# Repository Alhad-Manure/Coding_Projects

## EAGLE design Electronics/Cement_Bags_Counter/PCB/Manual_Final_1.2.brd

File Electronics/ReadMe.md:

All Embedded Electronics related codes.

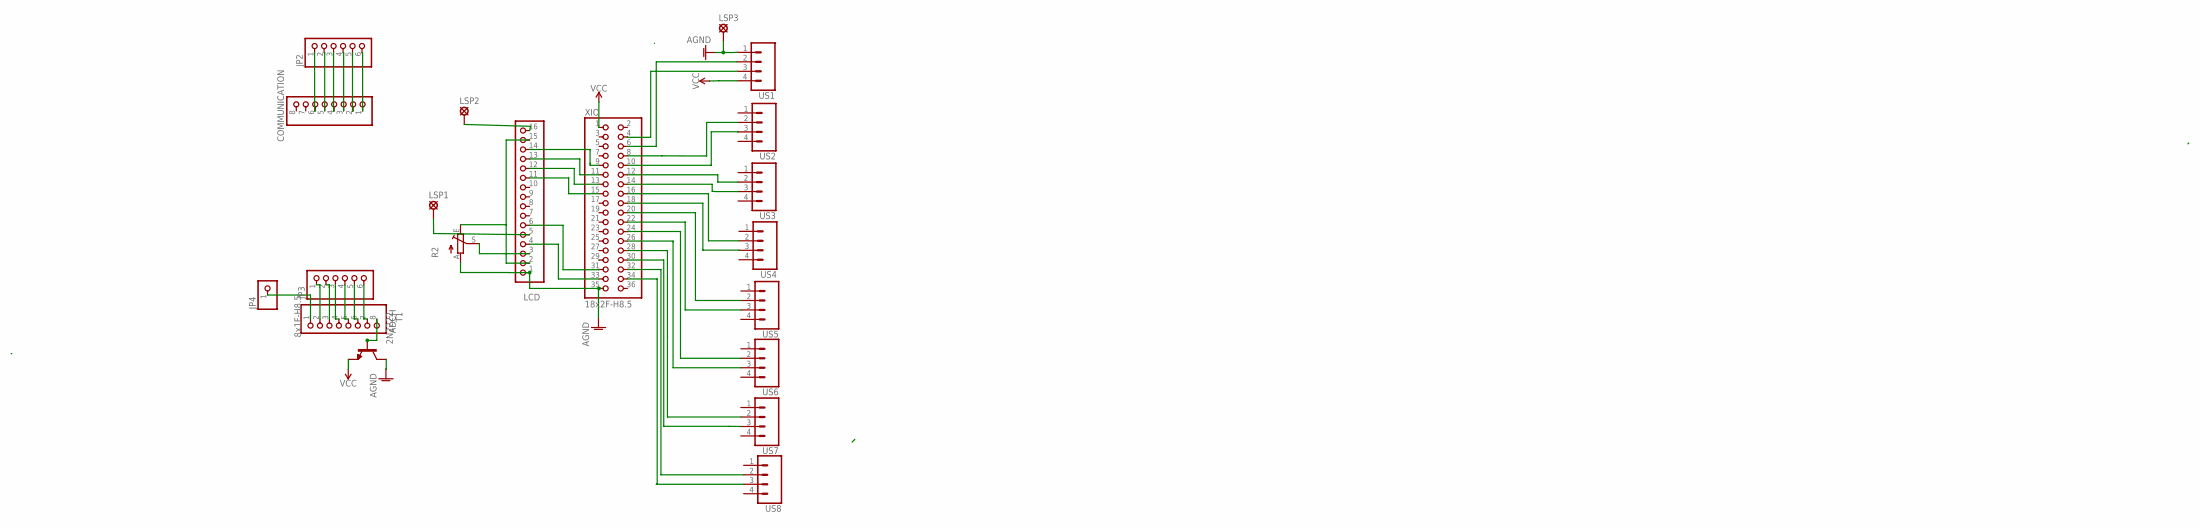
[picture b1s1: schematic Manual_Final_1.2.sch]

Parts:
ADCH: 8x1F-H8.5; 1X08
COMMUNICATION: 8x1F-H8.5; 1X08
JP2, JP3: PINHD-1X6; 1X06
JP4: PINHD-1X1; 1X01
LCD: PINHD-1X16; 1X16
LSP1, LSP2, LSP3: SE14
R2: TRIM_EU-RS3; RS3
T1: 2N2222; TO92-EBC-OVAL
US1, US2, US3, US4, US5, US6, US7, US8: CONN_04LOCK_LONGPADS; 1X04_LOCK_LONGPADS
XIO: 18x2F-H8.5; 2X18

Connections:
AGND: LCD.1, LSP3.MP, R2.A, T1.C, US1.1, XIO.35
unnamed: ADCH.8, T1.B
unnamed: COMMUNICATION.1, JP2.6
unnamed: US1.3, XIO.4
unnamed: US1.2, XIO.6
unnamed: US2.2, XIO.8
unnamed: US2.3, XIO.10
unnamed: US3.2, XIO.12
unnamed: US5.2, XIO.20
unnamed: US4.2, XIO.16
unnamed: US4.3, XIO.18
unnamed: US5.3, XIO.22
unnamed: US6.2, XIO.24
unnamed: US6.3, XIO.26
unnamed: US7.2, XIO.28
unnamed: US7.3, XIO.30
unnamed: US8.2, XIO.32
unnamed: US3.3, XIO.14
unnamed: US8.3, XIO.34
unnamed: LCD.2, LCD.15, R2.E
unnamed: LCD.3, R2.S
unnamed: LCD.4, XIO.33
unnamed: LCD.6, XIO.31
unnamed: LCD.14, XIO.9
unnamed: LCD.13, XIO.11
unnamed: LCD.12, XIO.13
unnamed: COMMUNICATION.2, JP2.5
unnamed: COMMUNICATION.3, JP2.4
unnamed: COMMUNICATION.4, JP2.3
unnamed: COMMUNICATION.5, JP2.2
unnamed: COMMUNICATION.6, JP2.1
unnamed: ADCH.7, JP3.6
unnamed: ADCH.6, JP3.5
unnamed: LCD.16, LSP2.MP
unnamed: LCD.5, LSP1.MP
unnamed: LCD.11, XIO.15
unnamed: ADCH.5, JP3.4
unnamed: ADCH.4, JP3.3
unnamed: ADCH.3, JP3.2
unnamed: ADCH.2, JP3.1
unnamed: ADCH.1, JP4.1
VCC: T1.E, US1.4, XIO.1

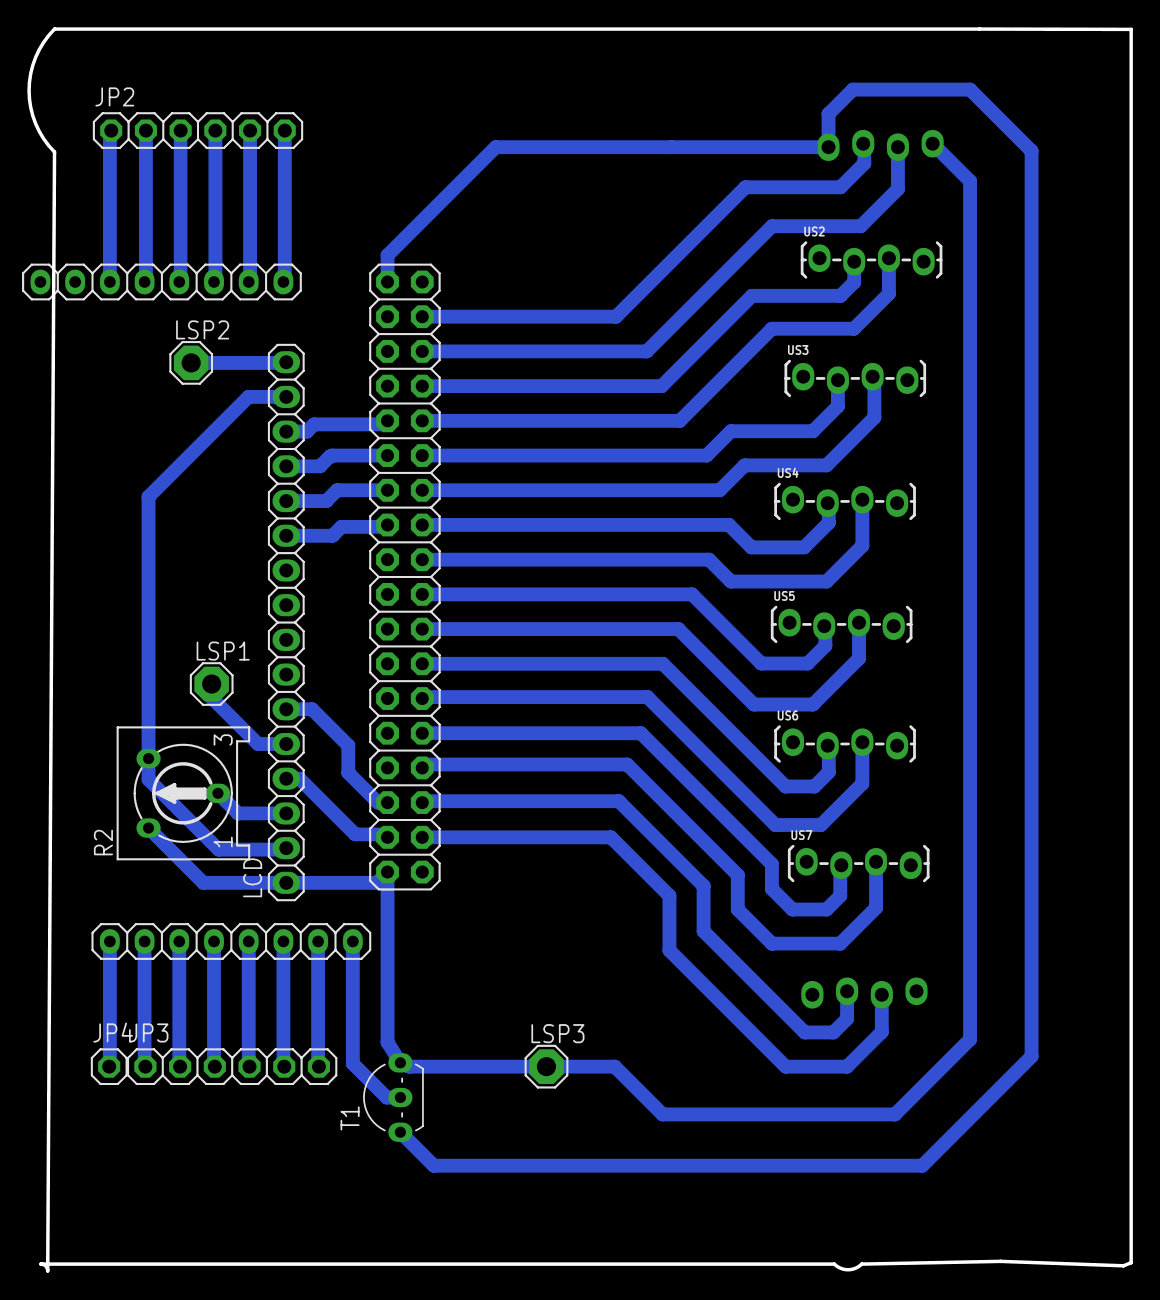
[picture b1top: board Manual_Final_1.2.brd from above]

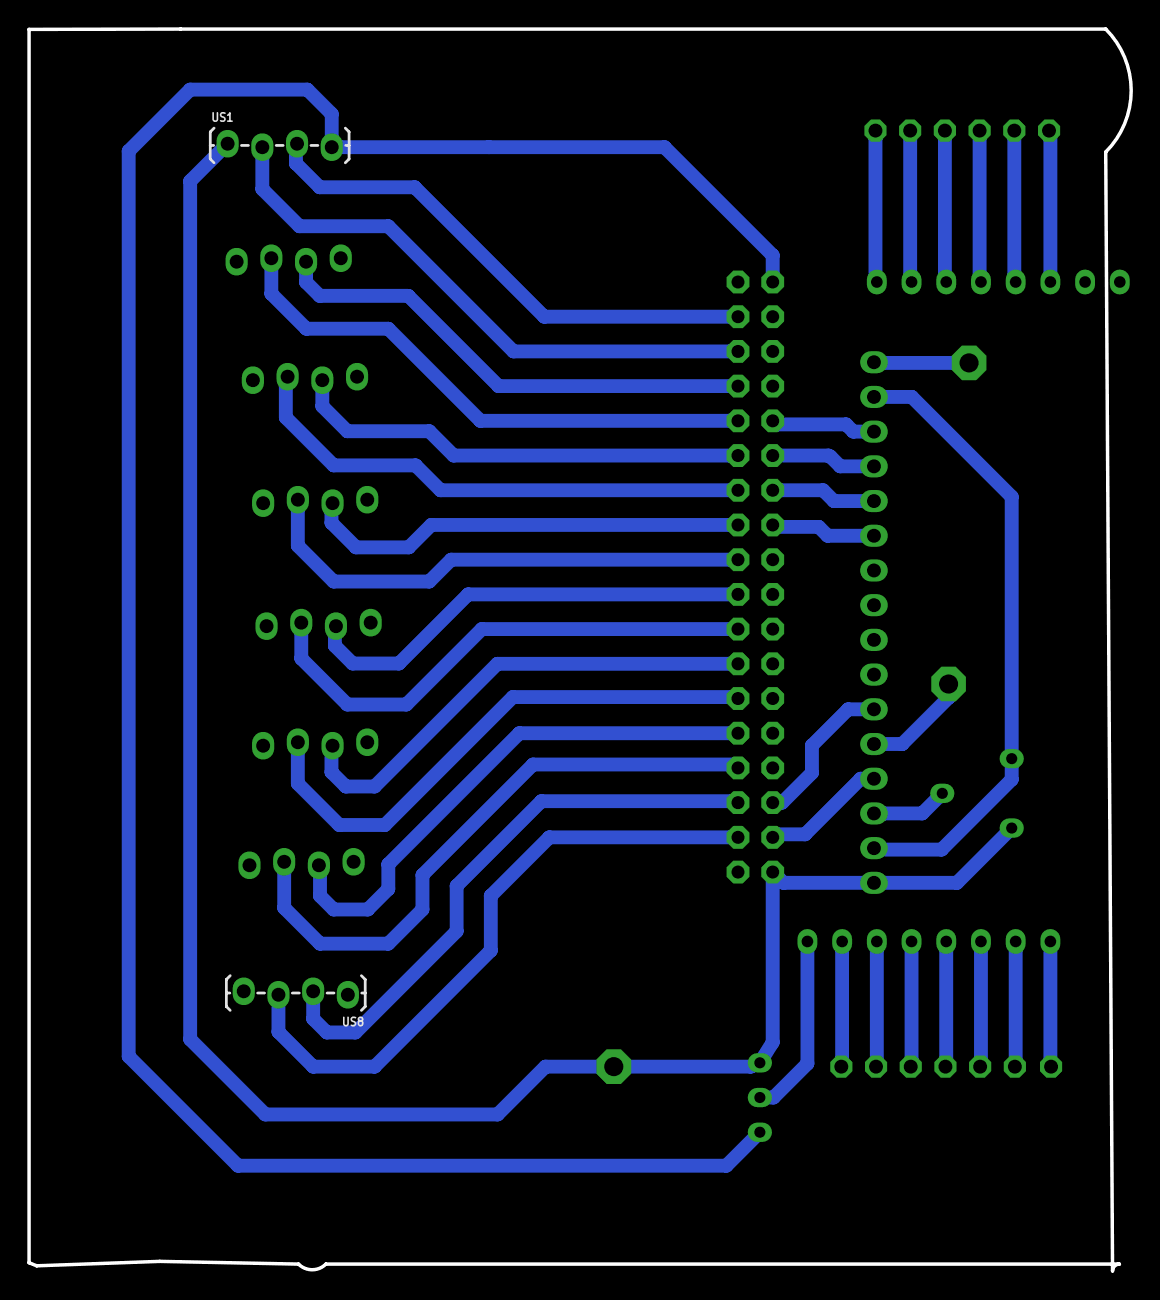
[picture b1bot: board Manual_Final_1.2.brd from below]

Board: 2 copper layers, 80.7 x 90.9 mm, 20 parts (2 on the bottom side), 42 nets.

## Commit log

2021-11-13 Rename Musical_Dancing_LEDs_&_Fountain/Musical_Multi_LEDs_Fountain2/Musical_Multi_LEDs_Fountain2.ino to Musical_Dancing_LEDs_&_Fountain/Musical_Multi_LEDs_Fountain/Musical_Multi_LEDs_Fountain.ino
2021-11-13 Create Musical_Dancing_LEDs
2021-11-13 Rename Holonomic_Drive/Manual_Drive_Without_encoder_4/Manual_Drive_Without_encoder_4.ino to Holonomic_Drive/Manual_Drive_Without_encoder/Manual_Drive_Without_encoder.ino
2022-04-13 Rename Holonomic_Drive/Manual_Drive_Without_encoder/Manual_Drive_Without_encoder.ino to Electronics/Holonomic_Drive/Manual_Drive_Without_encoder/Manual_Drive_Without_encoder.ino
2022-04-13 Rename Multi_Terrain_Robot/Robot_Car/Robot_Car.ino to Electronics/Multi_Terrain_Robot/Robot_Car/Robot_Car.ino
2022-04-13 Rename Multi_Terrain_Robot/Remote_Controle/Remote_Controle.ino to Electronics/Multi_Terrain_Robot/Remote_Controle/Remote_Controle.ino
2022-04-13 Rename Musical_Dancing_LEDs_&_Fountain/Musical_Multi_LEDs_Fountain/Musical_Multi_LEDs_Fountain.ino to Electronics/Musical_Dancing_LEDs_&_Fountain/Musical_Multi_LEDs_Fountain/Musical_Multi_LEDs_Founta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
2022-04-13 Rename Musical_Dancing_LEDs_&_Fountain/Musical_Spectrum_LEDs_Fountain/Musical_Spectrum_LEDs_Fountain.ino to Electronics/Musical_Dancing_LEDs_&_Fountain/Musical_Spectrum_LEDs_Fountain/Musical_Spectrum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
2022-04-13 Rename SecurityCam/CameraWeb/CameraWeb.ino to Electronics/SecurityCam/CameraWeb/Musical_Spectrum_LEDs_Fountain.ino
2022-04-13 Rename Musical_Spectrum_LEDs_Fountain.ino to CameraWeb5.ino
2022-04-13 Rename SecurityCam/CameraWeb/app_httpd.cpp to Electronics/SecurityCam/CameraWeb/app_httpd.cpp
2022-04-13 Rename SecurityCam/CameraWeb/camera_index.h to Electronics/SecurityCam/CameraWeb/camera_index.h
2022-04-13 Rename SecurityCam/CameraWeb/camera_pins.h to Electronics/SecurityCam/CameraWeb/camera_pins.h
2022-04-13 Rename SecurityCam/CameraWeb5/CameraWeb5.ino to Electronics/SecurityCam/CameraWeb5/CameraWeb5.ino
2022-04-13 Rename SecurityCam/NodeJsRemoteStream/client.html to Electronics/SecurityCam/NodeJsRemoteStream/client.html
2022-04-13 Rename SecurityCam/NodeJsRemoteStream/package-lock.json to Electronics/SecurityCam/NodeJsRemoteStream/package-lock.json
2022-04-13 Rename SecurityCam/NodeJsRemoteStream/package.json to Electronics/SecurityCam/NodeJsRemoteStream/package.json
2022-04-13 Rename SecurityCam/NodeJsRemoteStream/server.js to Electronics/SecurityCam/NodeJsRemoteStream/server.js
2022-04-13 Rename WiFi_Controlled_Festive_Lights/WiFi_Controlled_Festive_Lights.ino to Electronics/WiFi_Controlled_Festive_Lights/WiFi_Controlled_Festive_Lights.ino
2022-04-13 Rename Water_Level_Controller/Water_Level_Controller.ino to Electronics/Water_Level_Controller/Water_Level_Controller.ino
2022-07-10 Youtube Links of Project Demo
2022-07-10 Youtube link of Project demo
2022-07-10 Youtub links of Project demo
2023-11-30 Rename CricketScoreSheetMy1.exe to CricketScoreSheetMy.exe
2023-12-02 Rename CricketScoreSheetMy.exe to CricketScoreSheet.exe
2024-06-11 Latest changes
2024-06-11 new commit
2025-09-13 Creating windows build build-windows.yml file

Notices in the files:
parts and their libraries:
SparkFun-Connectors: Licensing: Creative Commons ShareAlike 4.0 International - https://creativecommons.org/licenses/by-sa/4.0
